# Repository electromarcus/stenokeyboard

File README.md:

# Stenography keyboard
A custom specialty keyboard that will work with Plover, an open source stenography software, that lets me type much faster and type whole words at once. It will use a raspberry pi pico and a custom case that I design, along with some keyboard switches, and some LEDs in the case for aesthetics, and a PCB to connect it all. It is wired so doesn't need batteries, but does need Plover to be installed on the computer it connects to.

PCB:

PCB Schematic:

CAD Picture:

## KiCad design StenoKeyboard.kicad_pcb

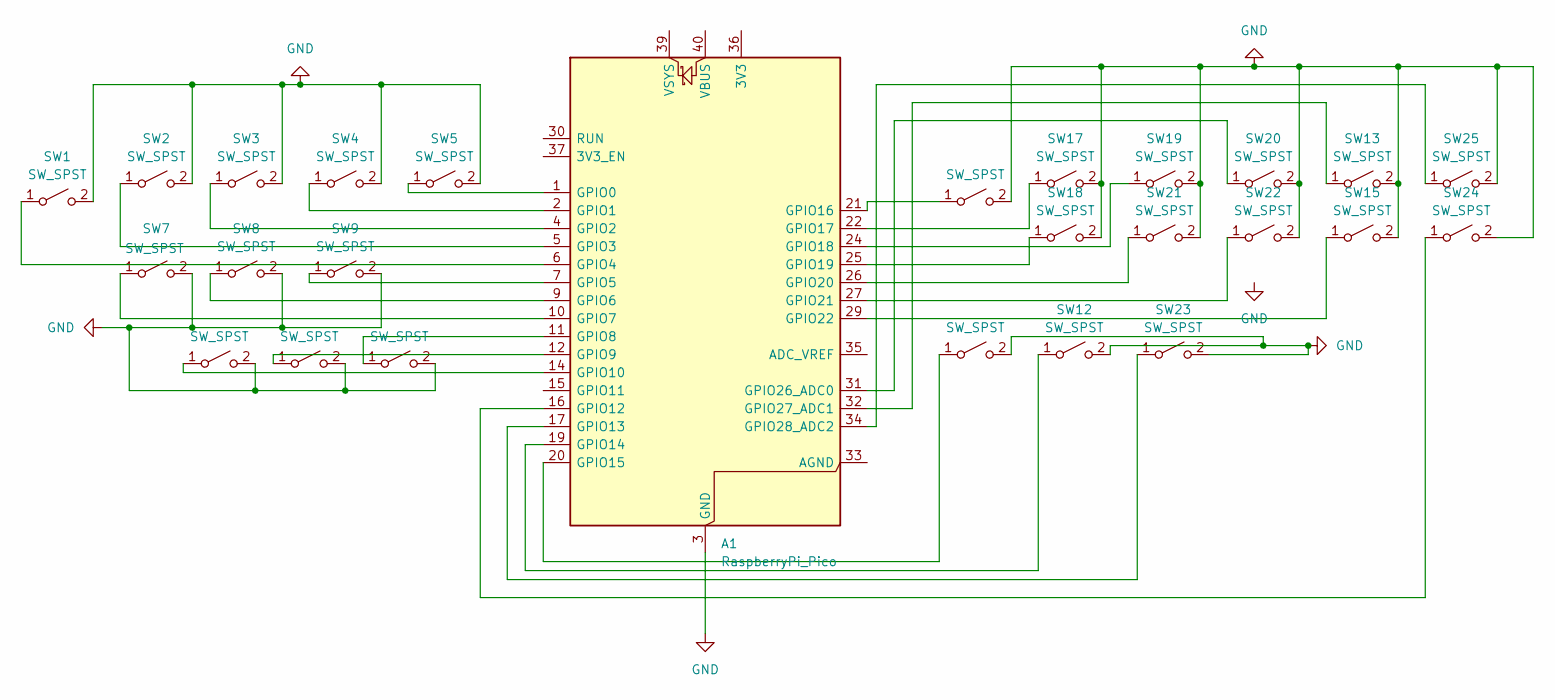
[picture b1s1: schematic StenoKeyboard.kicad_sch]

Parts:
A1: RaspberryPi_Pico; RaspberryPi_Pico_Common_Unspecified
SW1, SW2, SW3, SW4, SW5, SW6, SW7, SW8, SW9, SW10, SW11, SW12, SW13, SW14, SW15, SW16, SW17, SW18, SW19, SW20, SW21, SW22, SW23, SW24, SW25: SW_SPST; Gateron-KS33-Solderable-1U

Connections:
GND: A1.3 (GND), A1.8 (GND), A1.13 (GND), A1.18 (GND), A1.23 (GND), A1.28 (GND), A1.38 (GND), SW1.2 (B), SW2.2 (B), SW3.2 (B), SW4.2 (B), SW5.2 (B), SW6.2 (B), SW7.2 (B), SW8.2 (B), SW9.2 (B), SW10.2 (B), SW11.2 (B), SW12.2 (B), SW13.2 (B), SW14.2 (B), SW15.2 (B), SW16.2 (B), SW17.2 (B), SW18.2 (B), SW19.2 (B), SW20.2 (B), SW21.2 (B), SW22.2 (B), SW23.2 (B), SW24.2 (B), SW25.2 (B)
unnamed: A1.1 (GPIO0), SW5.1 (A)
unnamed: A1.2 (GPIO1), SW4.1 (A)
unnamed: A1.4 (GPIO2), SW3.1 (A)
unnamed: A1.5 (GPIO3), SW2.1 (A)
unnamed: A1.6 (GPIO4), SW1.1 (A)
unnamed: A1.7 (GPIO5), SW9.1 (A)
unnamed: A1.9 (GPIO6), SW8.1 (A)
unnamed: A1.10 (GPIO7), SW7.1 (A)
unnamed: A1.11 (GPIO8), SW6.1 (A)
unnamed: A1.12 (GPIO9), SW10.1 (A)
unnamed: A1.14 (GPIO10), SW11.1 (A)
unnamed: A1.16 (GPIO12), SW24.1 (A)
unnamed: A1.17 (GPIO13), SW23.1 (A)
unnamed: A1.19 (GPIO14), SW12.1 (A)
unnamed: A1.20 (GPIO15), SW14.1 (A)
unnamed: A1.21 (GPIO16), SW16.1 (A)
unnamed: A1.22 (GPIO17), SW17.1 (A)
unnamed: A1.24 (GPIO18), SW19.1 (A)
unnamed: A1.25 (GPIO19), SW18.1 (A)
unnamed: A1.26 (GPIO20), SW21.1 (A)
unnamed: A1.27 (GPIO21), SW22.1 (A)
unnamed: A1.29 (GPIO22), SW15.1 (A)
unnamed: A1.31 (GPIO26_ADC0), SW20.1 (A)
unnamed: A1.32 (GPIO27_ADC1), SW13.1 (A)
unnamed: A1.34 (GPIO28_ADC2), SW25.1 (A)

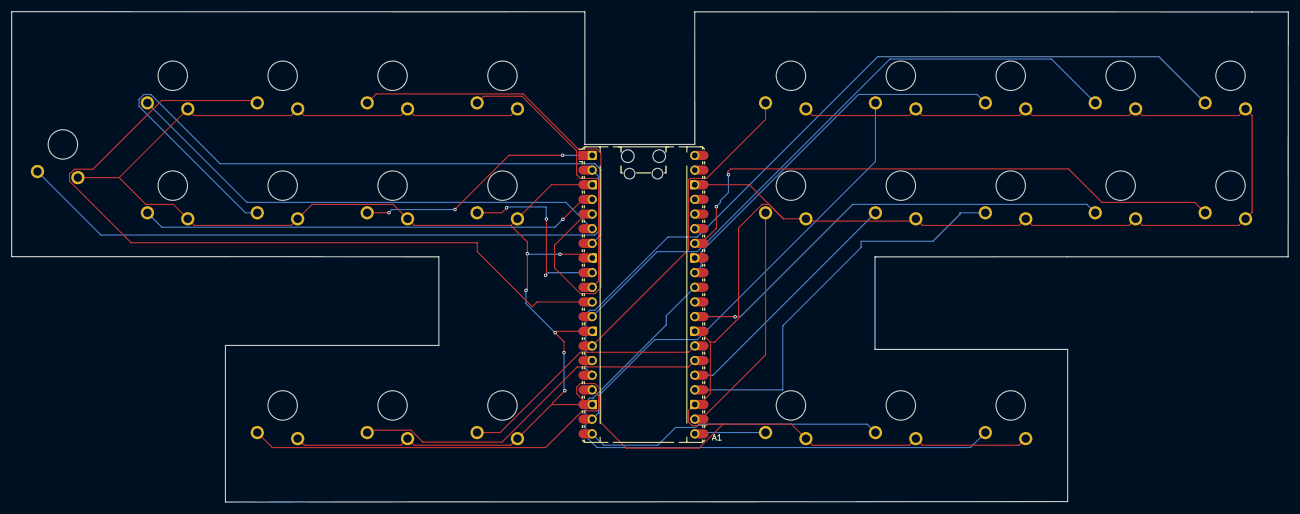
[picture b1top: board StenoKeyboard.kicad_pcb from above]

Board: 2 copper layers, 221.3 x 85.0 mm, 26 parts (0 on the bottom side), 26 nets.

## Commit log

2025-12-12 Rename BOM.md to TextBOM.md
2025-12-12 Rename StenoPCB.zip to GeberandDrillFiles.zip
2025-12-12 Rename Screen Shot 2025-12-12 at 10.30.43 PM.png to 3DModel
2025-12-13 Rename GeberandDrillFiles.zip to PCB Files/GeberandDrillFiles.zip
2025-12-13 Rename StenoKeyboard.kicad_pro to PCB Files/StenoKeyboard.kicad_pro
2025-12-13 Rename StenoKeyboardCaseModel.step to 3D Files/StenoKeyboardCaseModel.step
2025-12-13 Rename 3DModel to 3D File/Model Picture
2025-12-13 Rename Model Picture to Model Picture
2025-12-13 Rename TextBOM.md to BOM/TextBOM.md
2025-12-13 Create Link to Plover
2026-01-02 Rename Model Picture to Model Picture.png
